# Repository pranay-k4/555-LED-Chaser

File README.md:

# 555-LED-Chaser

A custom-designed 555 Timer LED Chaser PCB built using KiCad. The board uses a 555 timer to generate clock pulses and a counter IC to create a sequential LED chasing effect.

## Features

- Adjustable chase speed using potentiometer
- Two operating modes:
  - Sequential LED chaser
  - All LEDs ON
- Custom PCB designed in KiCad
- Beginner-friendly electronics project
- Through-hole components for easy assembly

## How It Works

The NE555 timer is configured in astable mode to generate periodic clock pulses.These pulses are fed into the counter IC, which activates the LEDs one after another, creating the chasing effect.The potentiometer changes the timing capacitor charging/discharging rate, allowing the user to control the chase speed.

## Modes

The mode button selects between:
- Sequential LED Chaser
- All LEDs ON

## Building it yourself

1. Download the Gerber files.
2. Manufacture the PCB.
3. Purchase components using the BOM.
4. Solder all components.
5. Apply power.
6. Adjust speed using the potentiometer.
7. Change modes using the push button.

### Schematics -

## PCB design - 

### Final 3D design - 

### Images:

## Demo Video
Youtube link: [here](https://youtu.be/frKLaEfmWBQ)

Part of Hack Club's Stasis Event

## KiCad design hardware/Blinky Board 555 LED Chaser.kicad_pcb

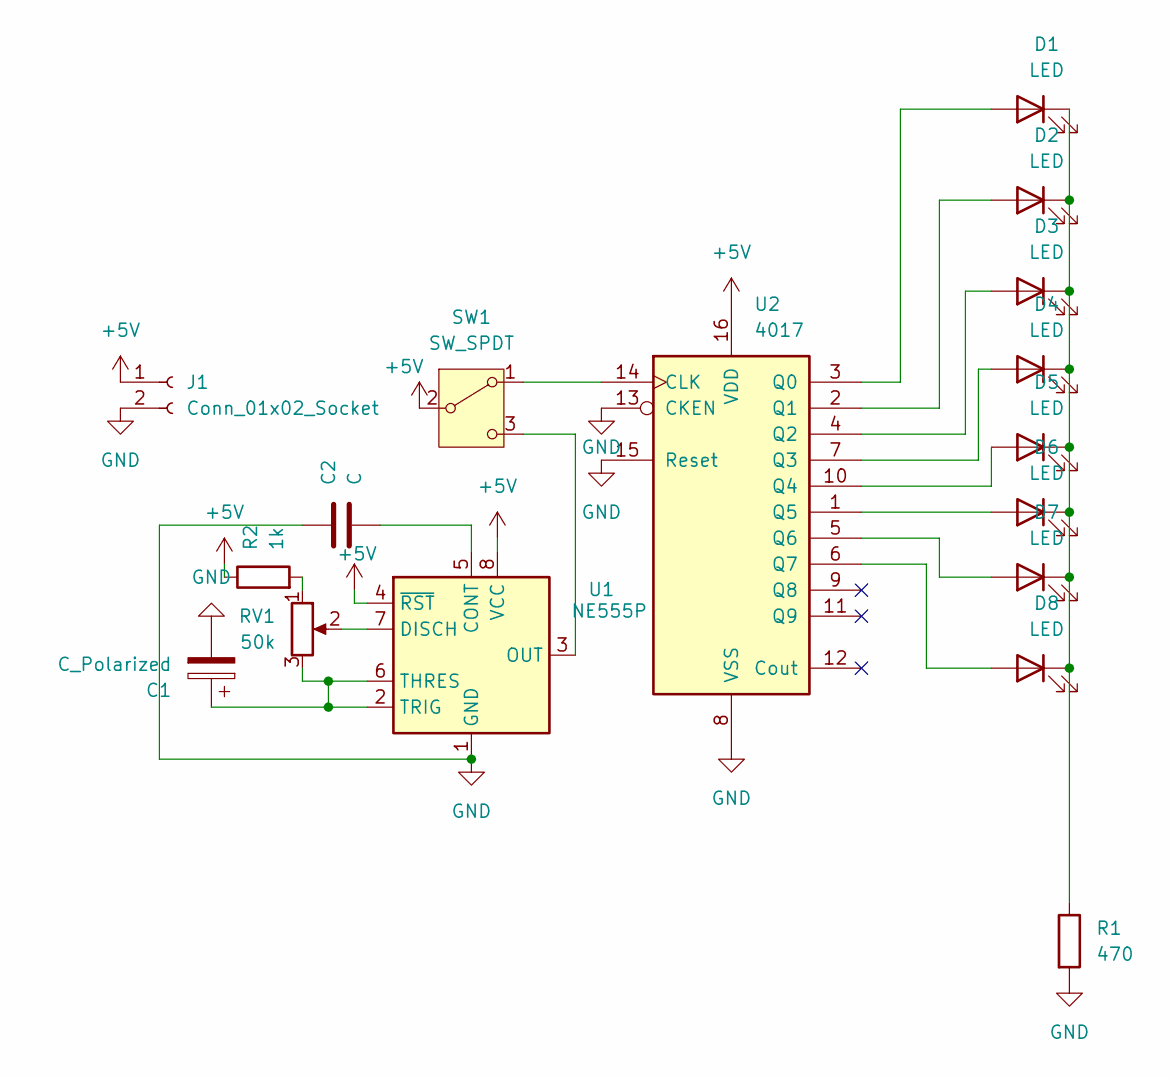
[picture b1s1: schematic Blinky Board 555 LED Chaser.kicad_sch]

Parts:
C1: C_Polarized; CP_Radial_D5.0mm_P2.50mm
C2: C; C_Disc_D5.0mm_W2.5mm_P2.50mm
D1, D2, D3, D4, D5, D6, D7, D8: LED; LED_D5.0mm
J1: Conn_01x02_Socket; PinHeader_1x02_P2.54mm_Horizontal
R1: 470; R_Axial_DIN0207_L6.3mm_D2.5mm_P7.62mm_Horizontal
R2: 1k; R_Axial_DIN0207_L6.3mm_D2.5mm_P7.62mm_Horizontal
RV1: 50k; Potentiometer_Bourns_3386P_Vertical
SW1: SW_SPDT; SW_Slide_SPDT_Straight_CK_OS102011MS2Q
U1: NE555P; DIP-8_W7.62mm
U2: 4017; DIP-16_W7.62mm

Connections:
+5V: J1.1, R2.1, SW1.2 (B), U1.4 (~RST), U1.8 (VCC), U2.16 (VDD)
GND: C1.2, C2.1, J1.2, R1.2, U1.1 (GND), U2.8 (VSS), U2.13 (CKEN), U2.15 (Reset)
unnamed: D1.2 (A), U2.3 (Q0)
unnamed: D1.1 (K), D2.1 (K), D3.1 (K), D4.1 (K), D5.1 (K), D6.1 (K), D7.1 (K), D8.1 (K), R1.1
unnamed: D2.2 (A), U2.2 (Q1)
unnamed: D3.2 (A), U2.4 (Q2)
unnamed: D4.2 (A), U2.7 (Q3)
unnamed: D5.2 (A), U2.10 (Q4)
unnamed: D6.2 (A), U2.1 (Q5)
unnamed: D7.2 (A), U2.5 (Q6)
unnamed: D8.2 (A), U2.6 (Q7)
unnamed: R2.2, RV1.1
unnamed: SW1.1 (A), U2.14 (CLK)
unnamed: SW1.3 (C), U1.3 (OUT)
unnamed: C2.2, U1.5 (CONT)
unnamed: RV1.2, U1.7 (DISCH)
unnamed: C1.1, RV1.3, U1.2 (TRIG), U1.6 (THRES)

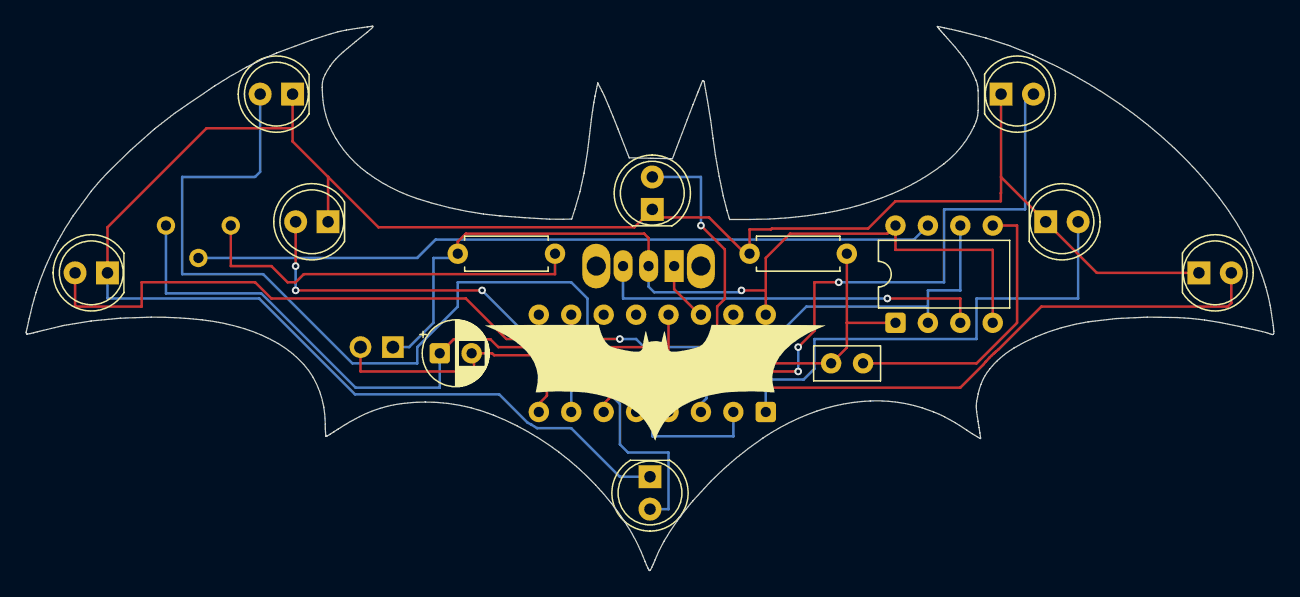
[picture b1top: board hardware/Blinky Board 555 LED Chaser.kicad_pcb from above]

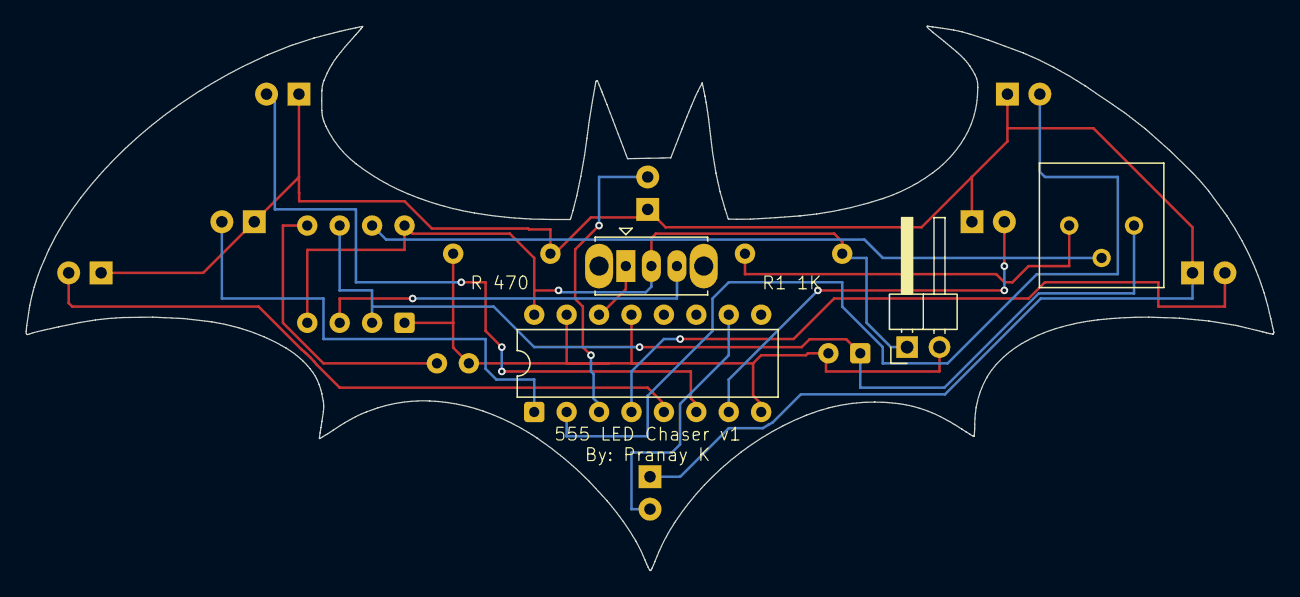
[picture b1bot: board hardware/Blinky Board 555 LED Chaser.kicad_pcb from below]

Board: 2 copper layers, 97.7 x 42.6 mm, 17 parts (4 on the bottom side), 17 nets.

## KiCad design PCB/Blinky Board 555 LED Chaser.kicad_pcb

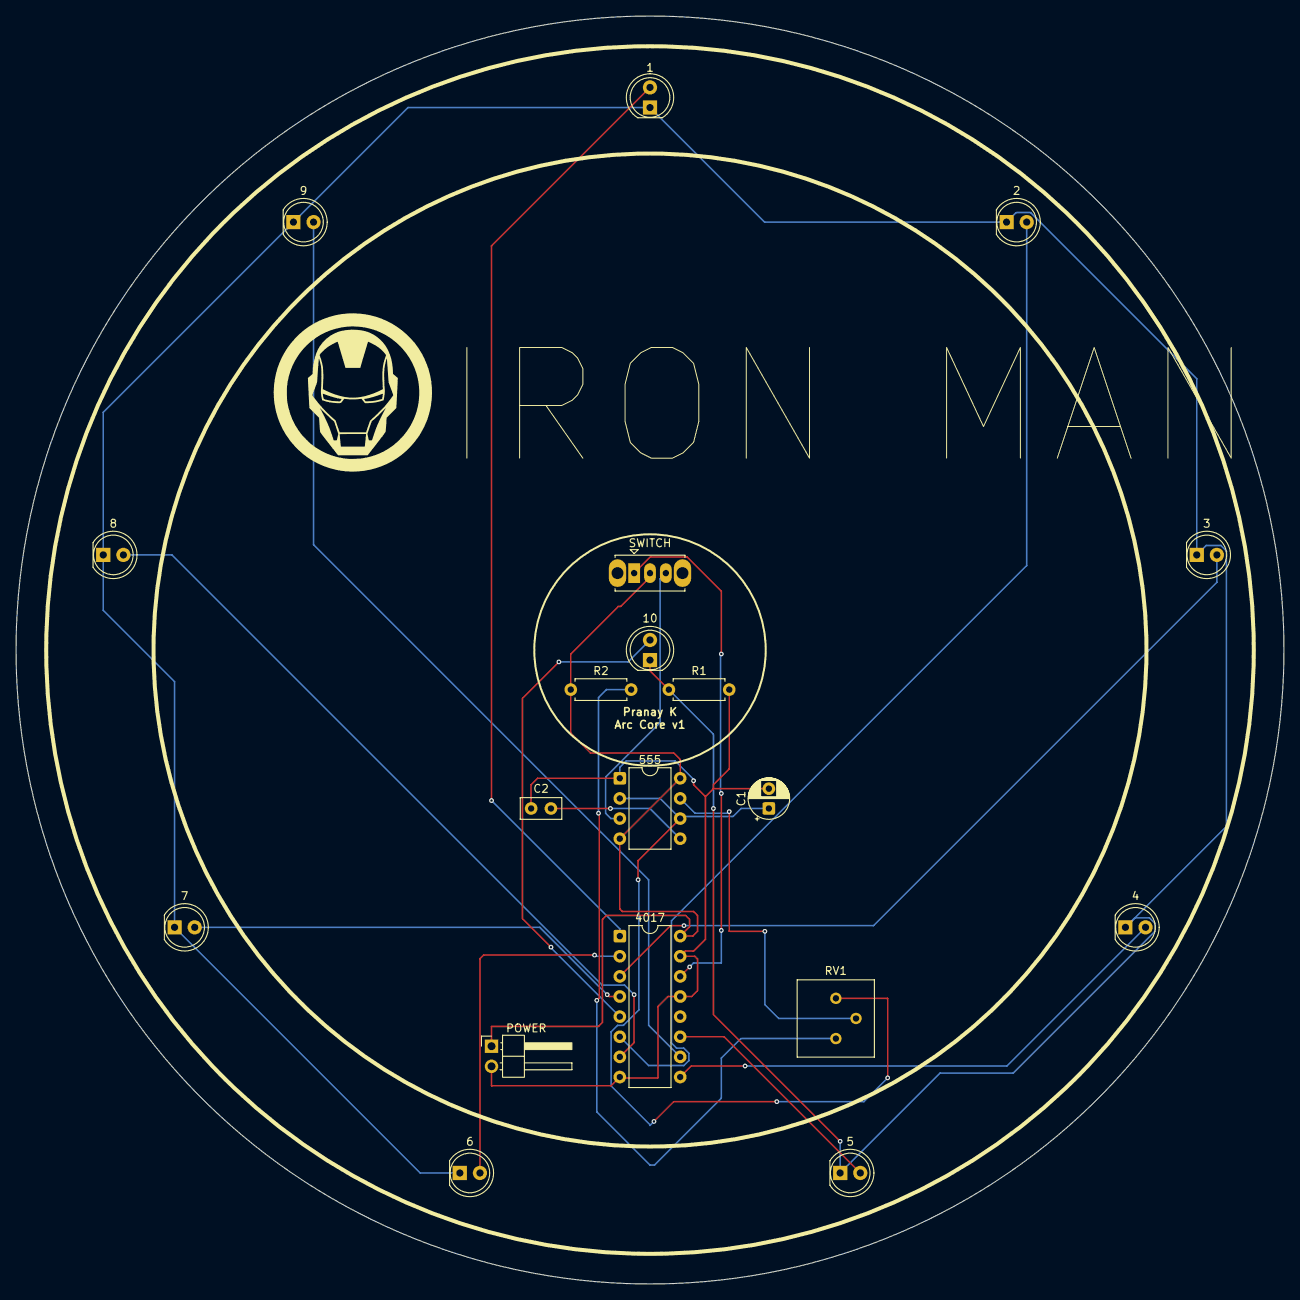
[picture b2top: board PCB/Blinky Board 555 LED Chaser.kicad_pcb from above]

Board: 2 copper layers, 160.0 x 160.0 mm, 21 parts (1 on the bottom side), 19 nets.

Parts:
1, 2, 3, 4, 5, 6, 7, 8, 9, 10: LED; LED_D5.0mm
555: NE555P; DIP-8_W7.62mm
4017: 4017; DIP-16_W7.62mm
C1: C_Polarized; CP_Radial_D5.0mm_P2.50mm
C2: C; C_Disc_D5.0mm_W2.5mm_P2.50mm
IRONMAN: LOGO; finaltest
IRONMAN#2: LOGO; finaltest
POWER: Conn_01x02_Socket; PinHeader_1x02_P2.54mm_Horizontal
R1: 470; R_Axial_DIN0207_L6.3mm_D2.5mm_P7.62mm_Horizontal
R2: 1k; R_Axial_DIN0207_L6.3mm_D2.5mm_P7.62mm_Horizontal
RV1: 50k; Potentiometer_Bourns_3386P_Vertical
SWITCH: SW_SPDT; SW_Slide_SPDT_Straight_CK_OS102011MS2Q

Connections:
+5V: 555.4 (~RST), 555.8 (VCC), 4017.16 (VDD), POWER.1, R2.1, SWITCH.2 (B)
GND: 555.1 (GND), 4017.8 (VSS), 4017.13 (CKEN), 4017.15 (Reset), C1.2, C2.1, POWER.2, R1.2
unnamed: 3.2 (A), 4017.3 (Q0)
unnamed: 1.1 (K), 2.1 (K), 3.1 (K), 4.1 (K), 5.1 (K), 6.1 (K), 7.1 (K), 8.1 (K), 9.1 (K), 10.1 (K), R1.1
unnamed: 6.2 (A), 4017.2 (Q1)
unnamed: 7.2 (A), 4017.4 (Q2)
unnamed: 8.2 (A), 4017.7 (Q3)
unnamed: 9.2 (A), 4017.10 (Q4)
unnamed: 1.2 (A), 4017.1 (Q5)
unnamed: 10.2 (A), 4017.5 (Q6)
unnamed: 2.2 (A), 4017.6 (Q7)
unnamed: 4.2 (A), 4017.9 (Q8)
unnamed: 5.2 (A), 4017.11 (Q9)
unnamed: R2.2, RV1.1
unnamed: 4017.14 (CLK), SWITCH.1 (A)
unnamed: 555.3 (OUT), SWITCH.3 (C)
unnamed: 555.5 (CONT), C2.2
unnamed: 555.7 (DISCH), RV1.2
unnamed: 555.2 (TRIG), 555.6 (THRES), C1.1, RV1.3

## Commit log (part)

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2026-04-07 Create a
2026-05-10 Rename 555 Led Chaser v2.zip to docs/555 Led Chaser v2 Gerbers.zip
2026-05-10 Rename Blinky Board 555 LED Chaser.kicad_pcb to docs/Blinky Board 555 LED Chaser.kicad_pcb
2026-05-10 Rename Blinky Board 555 LED Chaser.kicad_sch to docs/Blinky Board 555 LED Chaser.kicad_sch
2026-05-10 Rename My Blinky Board PCB-bom.csv to docs/My Blinky Board PCB-bom.csv
2026-05-10 Create LICENSE
2026-05-10 Rename docs/My Blinky Board PCB-bom.csv to BOM.csv
2026-05-10 Rename 555 Led Chaser v2 Gerbers.zip to 555 Led Chaser v2 Gerbers.zip
2026-05-10 Rename Blinky Board 555 LED Chaser.kicad_pcb to Blinky Board 555 LED Chaser.kicad_pcb
2026-05-10 Rename Blinky Board 555 LED Chaser.kicad_sch to Blinky Board 555 LED Chaser.kicad_sch
2026-05-10 Rename JOURNAL.md to JOURNAL.md
